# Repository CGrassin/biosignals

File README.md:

# BioSignals

**This project is work-in-progress.**

BioSignals is a multi-channel, up to 24-bits resolution acquisition system for bio-potentials (EMG, ECG, EEG and more). 

Repository structure:
* **Firmware_BioSignals**: the firmware to be programmed on the board with STM32duino.
* **Electronics_BioSignals**: the circuit board files.
* **Software_BioSignals**: software for the host computer
* **CAD_BioSignals**: 3D files (EEG headware).
* **Interface.md**: description of the data and command interface to the board.

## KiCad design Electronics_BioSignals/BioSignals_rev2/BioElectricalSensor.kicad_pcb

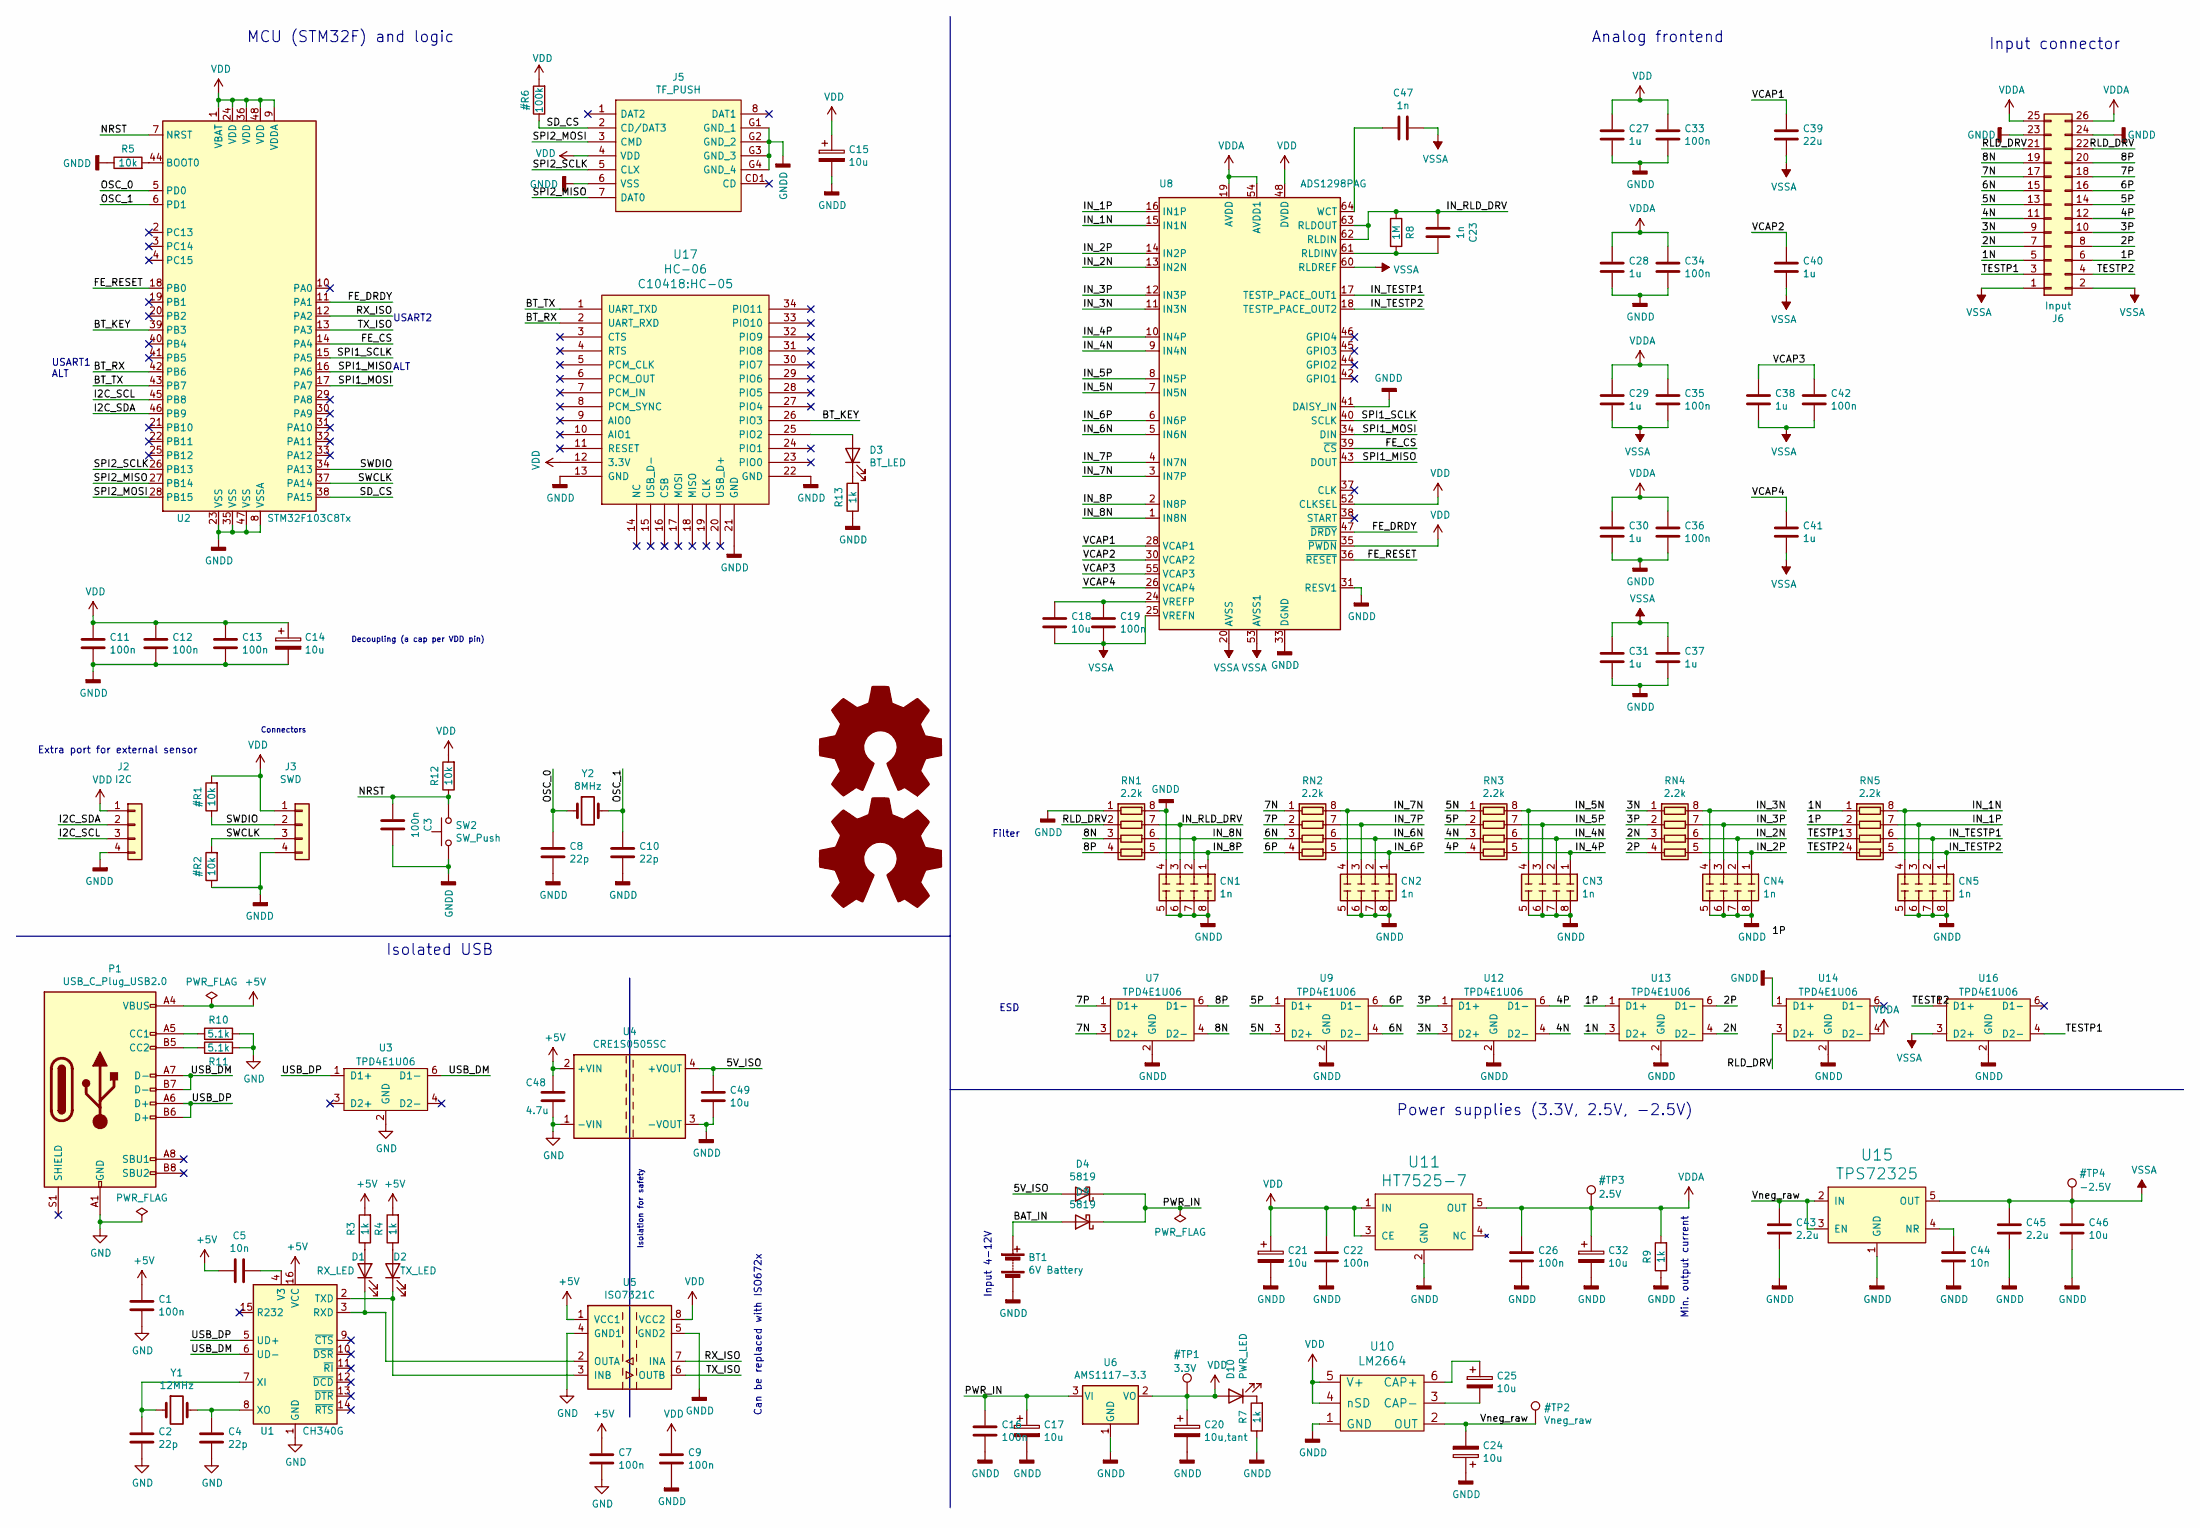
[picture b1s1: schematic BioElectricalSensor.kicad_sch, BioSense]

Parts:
BT1: 6V Battery; JST_XH_S2B-XH-A-1_1x02_P2.50mm_Horizontal
C1, C3, C7, C9, C11, C12, C13, C16, C19, C22, C26, C33, C34, C35, C36, C42: 100n; C_0805_2012Metric; LCSC C476766
C2, C4, C8, C10: 22p; C_0805_2012Metric; LCSC C24658
C5, C44: 10n; C_0805_2012Metric; LCSC C52278
C14, C17, C18, C21, C24, C25, C32, C46, C49: 10u; C_0805_2012Metric; LCSC C40894
C15: 10u; CP_Elec_5x5.4; LCSC C99837
C20: 10u,tant; CP_EIA-3216-10_Kemet-I; LCSC C110055
C23, C47: 1n; C_0805_2012Metric; LCSC C277515
C27, C28, C29, C30, C31, C37, C38, C40, C41: 1u; C_0805_2012Metric; LCSC C28323
C39: 22u; C_0805_2012Metric; LCSC C129302
C43, C45: 2.2u; C_0805_2012Metric; LCSC C87994
C48: 4.7u; C_0805_2012Metric; LCSC C1779
CN1, CN2, CN3, CN4, CN5: 1n; R_Array_Convex_4x0603; LCSC C507409
D1: RX_LED; LED_0805_2012Metric; LCSC C72037
D2: TX_LED; LED_0805_2012Metric; LCSC C72037
D3: BT_LED; LED_0805_2012Metric; LCSC C72037
D4, D9: 5819; D_SOD-123; LCSC C82544
D10: PWR_LED; LED_0805_2012Metric; LCSC C72037
J2: I2C; PinHeader_1x04_P2.54mm_Vertical
J3: SWD; PinHeader_1x04_P2.54mm_Vertical; LCSC C124378
J5: TF_PUSH; TFPUSH; Manufacturer_Part_Number TF PUSH; LCSC C393941
J6: Input; PinHeader_2x13_P2.54mm_Horizontal; LCSC C358714
LOGO1: Logo_Open_Hardware_Large; Charleslabs_Logo_5mm
LOGO2: Logo_Open_Hardware_Large; Charleslabs_Logo_10mm
P1: USB_C_Plug_USB2.0; USB_C_Receptacle_HRO_TYPE-C-31-M-12; LCSC C393939
R3, R4, R7, R9, R13: 1k; R_0805_2012Metric; LCSC C17513
R5, R12: 10k; R_0805_2012Metric; LCSC C38522
R8: 1M; R_0805_2012Metric; LCSC C17514
R10, R11: 5.1k; R_0805_2012Metric; LCSC C115337
RN1, RN2, RN3, RN4, RN5: 2.2k; R_Array_Convex_4x0603; LCSC C12001
SW2: SW_Push; SW_SPST_CK_RS282G05A3
U1: CH340G; SOIC-16_3.9x9.9mm_P1.27mm; LCSC C14267
U2: STM32F103C8Tx; LQFP-48_7x7mm_P0.5mm; LCSC C8734
U3, U7, U9, U12, U13, U14, U16: TPD4E1U06; SOT-23-6; LCSC C124691
U4: CRE1S0505SC; Converter_DCDC_muRata_CRE1xxxxxxSC_THT; LCSC C18424
U5: ISO7321C; SOIC-8_3.9x4.9mm_P1.27mm; LCSC C187919
U6: AMS1117-3.3; SOT-223-3_TabPin2; LCSC C6186
U8: ADS1298PAG; TQFP-64_10x10mm_P0.5mm
U10: LM2664; SOT-23-6; LCSC C108573
U11: HT7525-7; SOT-23-5; LCSC C259864
U15: TPS72325; SOT-23-5; LCSC C69932
U17: HC-06; HC-05
Y1: 12MHz; Crystal_SMD_5032-2Pin_5.0x3.2mm; LCSC C259045
Y2: 8MHz; Crystal_SMD_5032-2Pin_5.0x3.2mm; LCSC C259040

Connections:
+5V: C1.1, C5.2, C7.1, C48.1, P1.A4 (VBUS), P1.A9 (VBUS), P1.B4 (VBUS), P1.B9 (VBUS), R3.2, R4.2, U1.16 (VCC), U4.2 (+VIN), U5.1 (VCC1)
/1N: J6.5, RN5.1 (R1.1), U13.3 (D2+)
/1P: J6.6, RN5.2 (R2.1), U13.1 (D1+)
/2N: J6.7, RN4.3 (R3.1), U13.4 (D2-)
/2P: J6.8, RN4.4 (R4.1), U13.6 (D1-)
/3N: J6.9, RN4.1 (R1.1), U12.3 (D2+)
/3P: J6.10, RN4.2 (R2.1), U12.1 (D1+)
/4N: J6.11, RN3.3 (R3.1), U12.4 (D2-)
/4P: J6.12, RN3.4 (R4.1), U12.6 (D1-)
/5N: J6.13, RN3.1 (R1.1), U9.3 (D2+)
/5P: J6.14, RN3.2 (R2.1), U9.1 (D1+)
/5V_ISO: C49.1, D4.2 (A), U4.4 (+VOUT)
/6N: J6.15, RN2.3 (R3.1), U9.4 (D2-)
/6P: J6.16, RN2.4 (R4.1), U9.6 (D1-)
/7N: J6.17, RN2.1 (R1.1), U7.3 (D2+)
/7P: J6.18, RN2.2 (R2.1), U7.1 (D1+)
/8N: J6.19, RN1.3 (R3.1), U7.4 (D2-)
/8P: J6.20, RN1.4 (R4.1), U7.6 (D1-)
/BAT_IN: BT1.1 (+), D9.2 (A)
/BT_KEY: U2.39 (PB3), U17.26 (PIO3)
/BT_RX: U2.42 (PB6), U17.2 (UART_RXD)
/BT_TX: U2.43 (PB7), U17.1 (UART_TXD)
/FE_CS: U2.14 (PA4), U8.39 (~CS)
/FE_DRDY: U2.11 (PA1), U8.47 (~DRDY)
/FE_RESET: U2.18 (PB0), U8.36 (~RESET)
/I2C_SCL: J2.3, U2.45 (PB8)
/I2C_SDA: J2.2, U2.46 (PB9)
/IN_1N: CN5.4 (R4.1), RN5.8 (R1.2), U8.15 (IN1N)
/IN_1P: CN5.3 (R3.1), RN5.7 (R2.2), U8.16 (IN1P)
/IN_2N: CN4.2 (R2.1), RN4.6 (R3.2), U8.13 (IN2N)
/IN_2P: CN4.1 (R1.1), RN4.5 (R4.2), U8.14 (IN2P)
/IN_3N: CN4.4 (R4.1), RN4.8 (R1.2), U8.11 (IN3N)
/IN_3P: CN4.3 (R3.1), RN4.7 (R2.2), U8.12 (IN3P)
/IN_4N: CN3.2 (R2.1), RN3.6 (R3.2), U8.9 (IN4N)
/IN_4P: CN3.1 (R1.1), RN3.5 (R4.2), U8.10 (IN4P)
/IN_5N: CN3.4 (R4.1), RN3.8 (R1.2), U8.7 (IN5N)
/IN_5P: CN3.3 (R3.1), RN3.7 (R2.2), U8.8 (IN5P)
/IN_6N: CN2.2 (R2.1), RN2.6 (R3.2), U8.5 (IN6N)
/IN_6P: CN2.1 (R1.1), RN2.5 (R4.2), U8.6 (IN6P)
/IN_7N: CN2.4 (R4.1), RN2.8 (R1.2), U8.3 (IN7P)
/IN_7P: CN2.3 (R3.1), RN2.7 (R2.2), U8.4 (IN7N)
/IN_8N: CN1.2 (R2.1), RN1.6 (R3.2), U8.1 (IN8N)
/IN_8P: CN1.1 (R1.1), RN1.5 (R4.2), U8.2 (IN8P)
/IN_RLD_DRV: C23.2, CN1.3 (R3.1), R8.1, RN1.7 (R2.2), U8.62 (RLDIN), U8.63 (RLDOUT)
/IN_TESTP1: CN5.2 (R2.1), RN5.6 (R3.2), U8.17 (TESTP_PACE_OUT1)
/IN_TESTP2: CN5.1 (R1.1), RN5.5 (R4.2), U8.18 (TESTP_PACE_OUT2)
/NRST: C3.2, R12.1, SW2.2, U2.7 (NRST)
/OSC_0: C8.1, U2.5 (PD0), Y2.1
/OSC_1: C10.1, U2.6 (PD1), Y2.2
/PWR_IN: C16.1, C17.1, D4.1 (K), D9.1 (K), U6.3 (VI)
/RLD_DRV: J6.21, J6.22, RN1.2 (R2.1), U14.3 (D2+)
/RX_ISO: U2.12 (PA2), U5.7 (INA)
/SPI1_MISO: U2.16 (PA6), U8.43 (DOUT)
/SPI1_MOSI: U2.17 (PA7), U8.34 (DIN)
/SPI1_SCLK: U2.15 (PA5), U8.40 (SCLK)
/SPI2_MISO: J5.7 (DAT0), U2.27 (PB14)
/SPI2_MOSI: J5.3 (CMD), U2.28 (PB15)
/SPI2_SCLK: J5.5 (CLX), U2.26 (PB13)
/TESTP1: J6.3, RN5.3 (R3.1), U16.4 (D2-)
/TESTP2: J6.4, RN5.4 (R4.1), U16.1 (D1+)
/TX_ISO: U2.13 (PA3), U5.6 (OUTB)
/USB_DM: P1.A7 (D-), P1.B7 (D-), U1.6 (UD-), U3.6 (D1-)
/USB_DP: P1.A6 (D+), P1.B6 (D+), U1.5 (UD+), U3.1 (D1+)
/VCAP1: C39.1, U8.28 (VCAP1)
/VCAP2: C40.1, U8.30 (VCAP2)
/VCAP3: C38.1, C42.1, U8.55 (VCAP3)
/VCAP4: C41.1, U8.26 (VCAP4)
/Vneg_raw: C24.2, C43.1, U10.2 (OUT), U15.2 (IN), U15.3 (EN)
GND: C1.2, C2.2, C4.2, C7.2, C48.2, P1.A1 (GND), P1.A12 (GND), P1.B1 (GND), P1.B12 (GND), R10.2, R11.2, U1.1 (GND), U3.2 (GND), U4.1 (-VIN), U5.4 (GND1)
unnamed: C2.1, U1.7 (XI), Y1.1
unnamed: C4.1, U1.8 (XO), Y1.2
unnamed: C5.1, U1.4 (V3)
unnamed: C18.1, C19.1, U8.24 (VREFP)
unnamed: C23.1, R8.2, U8.61 (RLDINV)
unnamed: C25.1, U10.6 (CAP+)
unnamed: C25.2, U10.3 (CAP-)
unnamed: C44.1, U15.4 (NR)
unnamed: C47.2, U8.64 (WCT)
unnamed: D1.1 (K), U1.3 (RXD), U5.2 (OUTA)
unnamed: D1.2 (A), R3.1
unnamed: D2.1 (K), U1.2 (TXD), U5.3 (INB)
unnamed: D2.2 (A), R4.1
unnamed: D3.1 (K), R13.2
unnamed: D3.2 (A), U17.25 (PIO2)
unnamed: D10.1 (K), R7.2
unnamed: P1.A5 (CC1), R10.1
unnamed: P1.B5 (CC2), R11.1
unnamed: R5.2, U2.44 (BOOT0)
VDDA: C26.1, C28.1, C29.1, C30.1, C32.1, C34.1, C35.1, C36.1, J6.25, J6.26, R9.2, U8.19 (AVDD), U8.21 (AVDD), U8.22 (AVDD), U8.54 (AVDD1), U8.56 (AVDD), U8.59 (AVDD), U11.5 (OUT), U14.4 (D2-)
VSSA: C18.2, C19.2, C29.2, C31.1, C35.2, C37.1, C38.2, C39.2, C40.2, C41.2, C42.2, C45.1, C46.1, C47.1, J6.1, J6.2, U8.20 (AVSS), U8.23 (AVSS), U8.25 (VREFN), U8.32 (AVSS), U8.53 (AVSS1), U8.57 (AVSS), U8.58 (AVSS), U8.60 (RLDREF), U15.5 (OUT), U16.3 (D2+)

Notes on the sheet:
Power supplies (3.3V, 2.5V, -2.5V)
Decoupling (a cap per VDD pin)
Connectors
ESD
Input connector
USART1 ALT
USART2
ALT
MCU (STM32F) and logic
Min. output current
Analog frontend
Input 4-12V
Can be replaced with ISO672x
Isolation for safety
Filter
Isolated USB
Extra port for external sensor

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
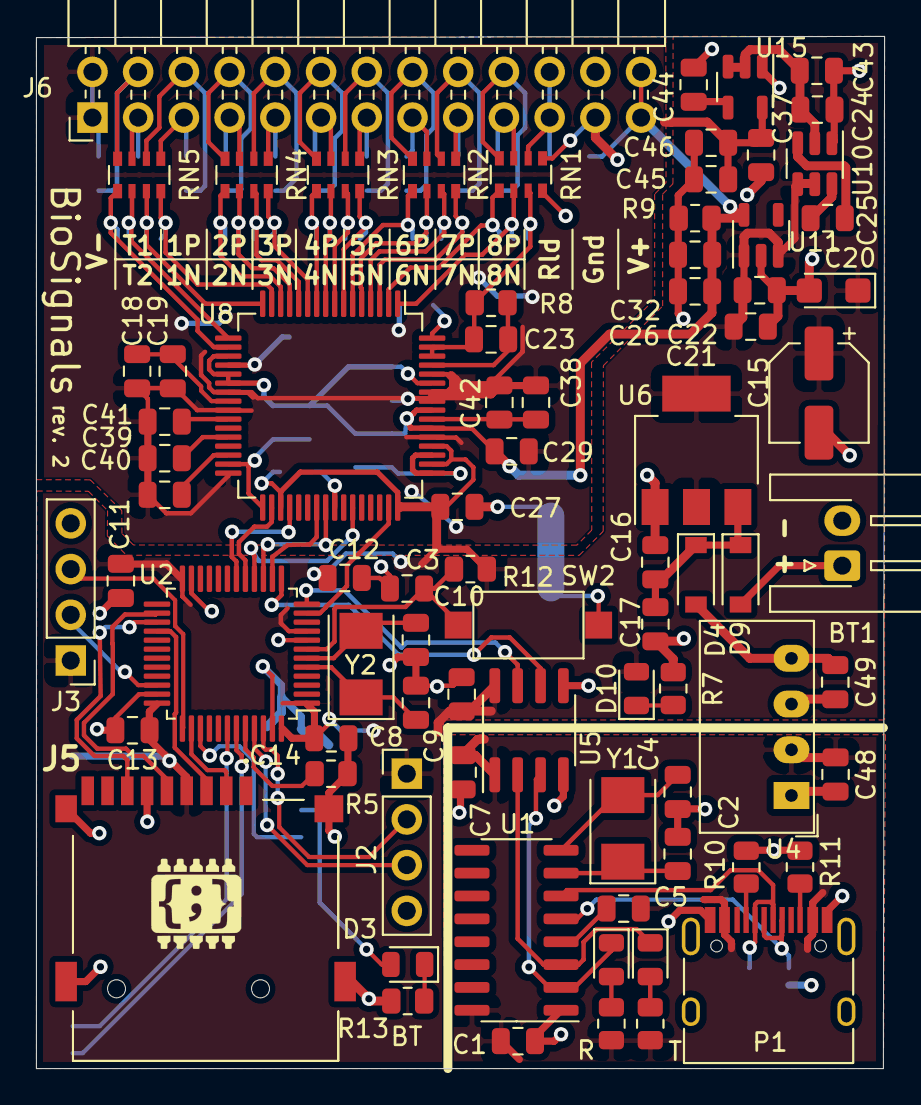
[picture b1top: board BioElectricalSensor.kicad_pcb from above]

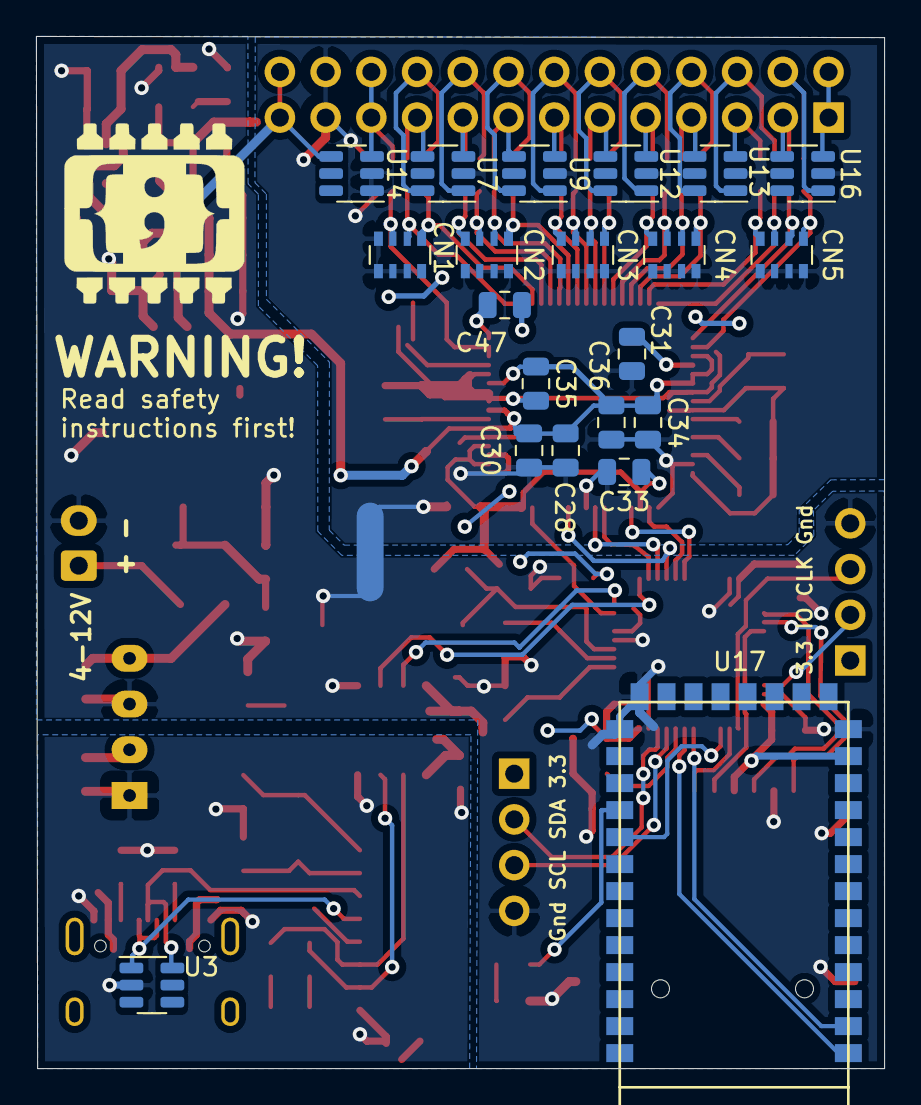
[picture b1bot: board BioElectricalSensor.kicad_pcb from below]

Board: 2 copper layers, 47.1 x 57.3 mm, 102 parts (22 on the bottom side), 95 nets.

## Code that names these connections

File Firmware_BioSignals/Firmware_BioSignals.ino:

#include <SPI.h>
#include <SdFat.h>
#include "openbci.h"

// Type of ADC:
// 0 for ADS1194, ADS1196, ADS1198 (UNTESTED).
// 1 for ADS1294, ADS1294R, ADS1296, ADS1296R, ADS1298, ADS1298R.
// 2 for ADS1299, ADS1299-4, ADS1299-6 (UNTESTED).
#define ADS_CHIP_TYPE 1

// Pinout for U2 (STM32F103C8Tx)
#define PIN_FE_DRDY PA1
#define PIN_FE_CS PA4
#define PIN_FE_RESET PB0
#define PIN_SPI1_SCLK PA5
#define PIN_SPI1_MISO PA6
#define PIN_SPI1_MOSI PA7

#define PIN_RX_ISO PA2 /* Connected to CH340 RX (TX on STM32) */
#define PIN_TX_ISO PA3 /* Connected to CH340 TX (RX on STM32) */

#define PIN_SD_CS PA15
#define PIN_SPI2_SCLK PB13
#define PIN_SPI2_MISO PB14
#define PIN_SPI2_MOSI PB15

#define PIN_BT_KEY PB3 /* Unused */
#define PIN_BT_RX PB6 /* Connected to HC-06 RX (TX on STM32) */
#define PIN_BT_TX PB7 /* Connected to HC-06 TX (RX on STM32) */

#define PIN_I2C_SCL PB8 /* Unused */
#define PIN_I2C_SDA PB9 /* Unused */

// TODO
// SD CARD

// CONFIG
//#define SD_CARD_ENABLE
#define SD_CARD_FILENAME "data.csv" // Warning: 8.3 format mandatory TBC
SPIClass SD_SPI2(PIN_SPI2_MOSI,PIN_SPI2_MISO,PIN_SPI2_SCLK);
File sd_file;
#define SD2_CONFIG SdSpiConfig(PIN_SD_CS, DEDICATED_SPI, SD_SCK_MHZ(18), &SD_SPI2)
SdFat SD;

HardwareSerial USB_SERIAL(PIN_TX_ISO, PIN_RX_ISO);
#define USB_SERIAL_SPEED 115200

HardwareSerial BT_SERIAL(PIN_BT_TX, PIN_BT_RX);
#define BT_SERIAL_SPEED 9600

SPIClass SPI1_FE(PIN_SPI1_MOSI,PIN_SPI1_MISO,PIN_SPI1_SCLK);
#if ADS_CHIP_TYPE == 0
  #include "ads119x.h"
  ADS119x ads = ADS119x(PIN_FE_CS, PIN_FE_DRDY, PIN_FE_RESET, &SPI1_FE);
#elif ADS_CHIP_TYPE == 1
  #include "ads129x.h"
  ADS129X ads = ADS129X(PIN_FE_CS, PIN_FE_DRDY, PIN_FE_RESET, &SPI1_FE);
#else
  #include "ads1299.h"
  ADS1299 ads = ADS1299(PIN_FE_CS, PIN_FE_DRDY, PIN_FE_RESET, &SPI1_FE);
#endif
OpenBCI openbci = OpenBCI(&ads, &USB_SERIAL);

void setup() {
  // USB ISO
  USB_SERIAL.begin(USB_SERIAL_SPEED);

  // Bluetooth
  BT_SERIAL.begin(BT_SERIAL_SPEED);

  // SD card (open card and file)
  #ifdef SD_CARD_ENABLE 
    if (SD.begin(SD2_CONFIG)) {
      sd_file = SD.open(SD_CARD_FILENAME, FILE_WRITE);
      if(sd_file){
        sd_file.println("Success!");
        sd_file.close();
        USB_SERIAL.println("Wrote to file");
      }
      else
       USB_SERIAL.println("Failed to create file");
    }
    else
       USB_SERIAL.println("Failed open SD");
  #endif

  // Init the OpenBCI and ADS
  openbci.init();
}

void loop() {
  if(ads.read_data()){
    openbci.sendData(ads.data);
  }
  openbci.readCMD();
}

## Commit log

2023-03-24 Initial firmware commit
2023-03-25 Added license
2023-03-25 Added documentation
2023-03-25 Added electronics rev1
2023-03-25 Added electronics rev2
2023-03-25 Added commands (d, D, V)
2023-03-25 Added other ADC support (implementation still missing)
2023-03-25 Fixed modularity of ADC support, added "0" command
2023-03-25 Added command "z" (LeadOff)
2023-03-25 Fixed LOFF and CONFIG3 default settings
2023-03-25 Fixed query command ("?")
2023-03-25 Added register map and config difference for ADS119X and ADS1299
2023-03-25 Added downsampling management, renamed defines for consistency
2023-03-25 Fixed sample rate command ("~")
2023-03-26 Proper support of sample rate implemented in ADS119x, refactoring
2023-03-26 Added CAD files
2023-03-26 Full implementation of "?" completed
2023-03-27 Better handling channel and sample rate defaults, refactoring
2023-03-27 Fixed channel setting function (unintentional recursion)
2023-03-27 Refactor process command function
2023-03-29 Added doxygen comments, 32kSPS mode
2023-03-29 Completed implementation of ADS1299
2023-03-29 Completed implementation of ADS119x
2023-03-29 Fixed bias register set
2023-03-31 Added FIR downsampling filter
2023-03-31 Added helper function to convert samples to standard integer
2023-03-31 Renamed symbols for consistency
2023-04-05 Fixed FIR filter implementation
